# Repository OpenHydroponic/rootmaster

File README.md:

# RootMaster

RootMaster is an open-source hydroponics system designed to help you grow plants efficiently using a soilless solution. This project aims to provide an affordable and customizable solution for home gardeners and small-scale farmers.

## Features

- Automated nutrient delivery system
- pH and EC monitoring
- Temperature and humidity control
- Remote monitoring and control via a web interface
- Modular design for easy expansion

## Documentation

https://openhydroponics.com/hw/rootmaster

## License

This project is licensed under the CERN Open Hardware License. See the [LICENSE](LICENSE) file for details.

## Contact

For questions or support, please open an issue on the [GitLab repository](https://gitlab.com/openhydroponics/hw/rootmaster/-/issues).

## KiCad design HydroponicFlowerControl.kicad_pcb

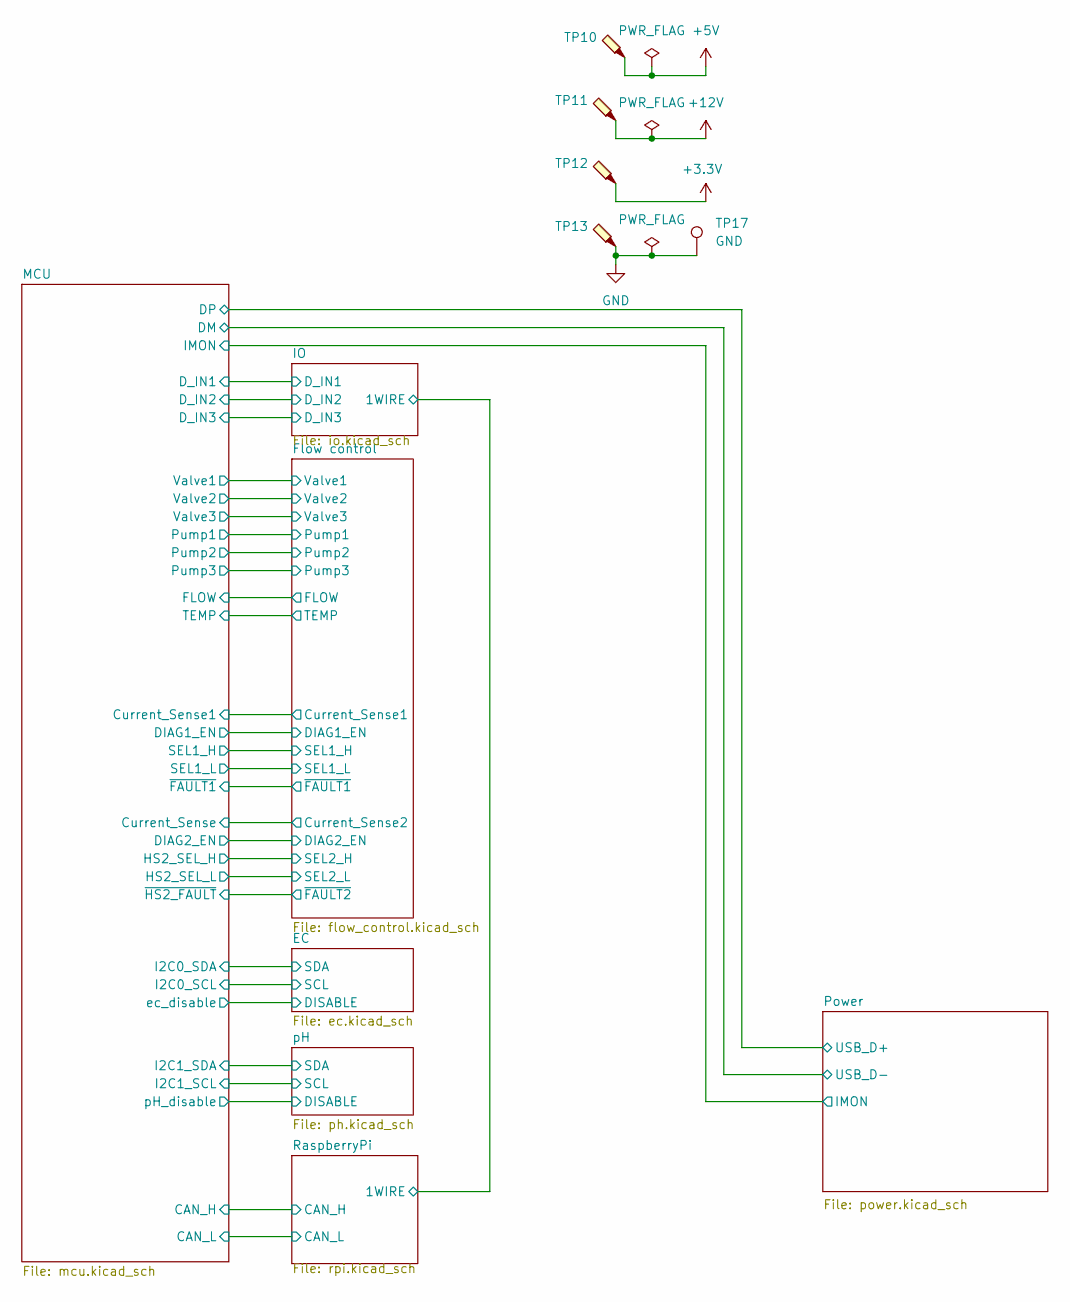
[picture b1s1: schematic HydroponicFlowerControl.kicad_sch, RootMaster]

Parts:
TP10: 5V; TestPoint_Pad_D1.0mm
TP11: 12V; TestPoint_Pad_D1.0mm
TP12: 3.3V; TestPoint_Pad_D1.0mm
TP13: GND; TestPoint_Loop_D1.80mm_Drill1.0mm_Beaded; LCSC C5199801
TP17: GND; TestPoint_Pad_D1.5mm

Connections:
+3.3V: TP12.1 (1_1); also elsewhere on the board
+5V: TP10.1 (1_1); also elsewhere on the board
+12V: TP11.1 (1_1); also elsewhere on the board
GND: TP13.1 (1_1), TP17.1 (1_1); also elsewhere on the board

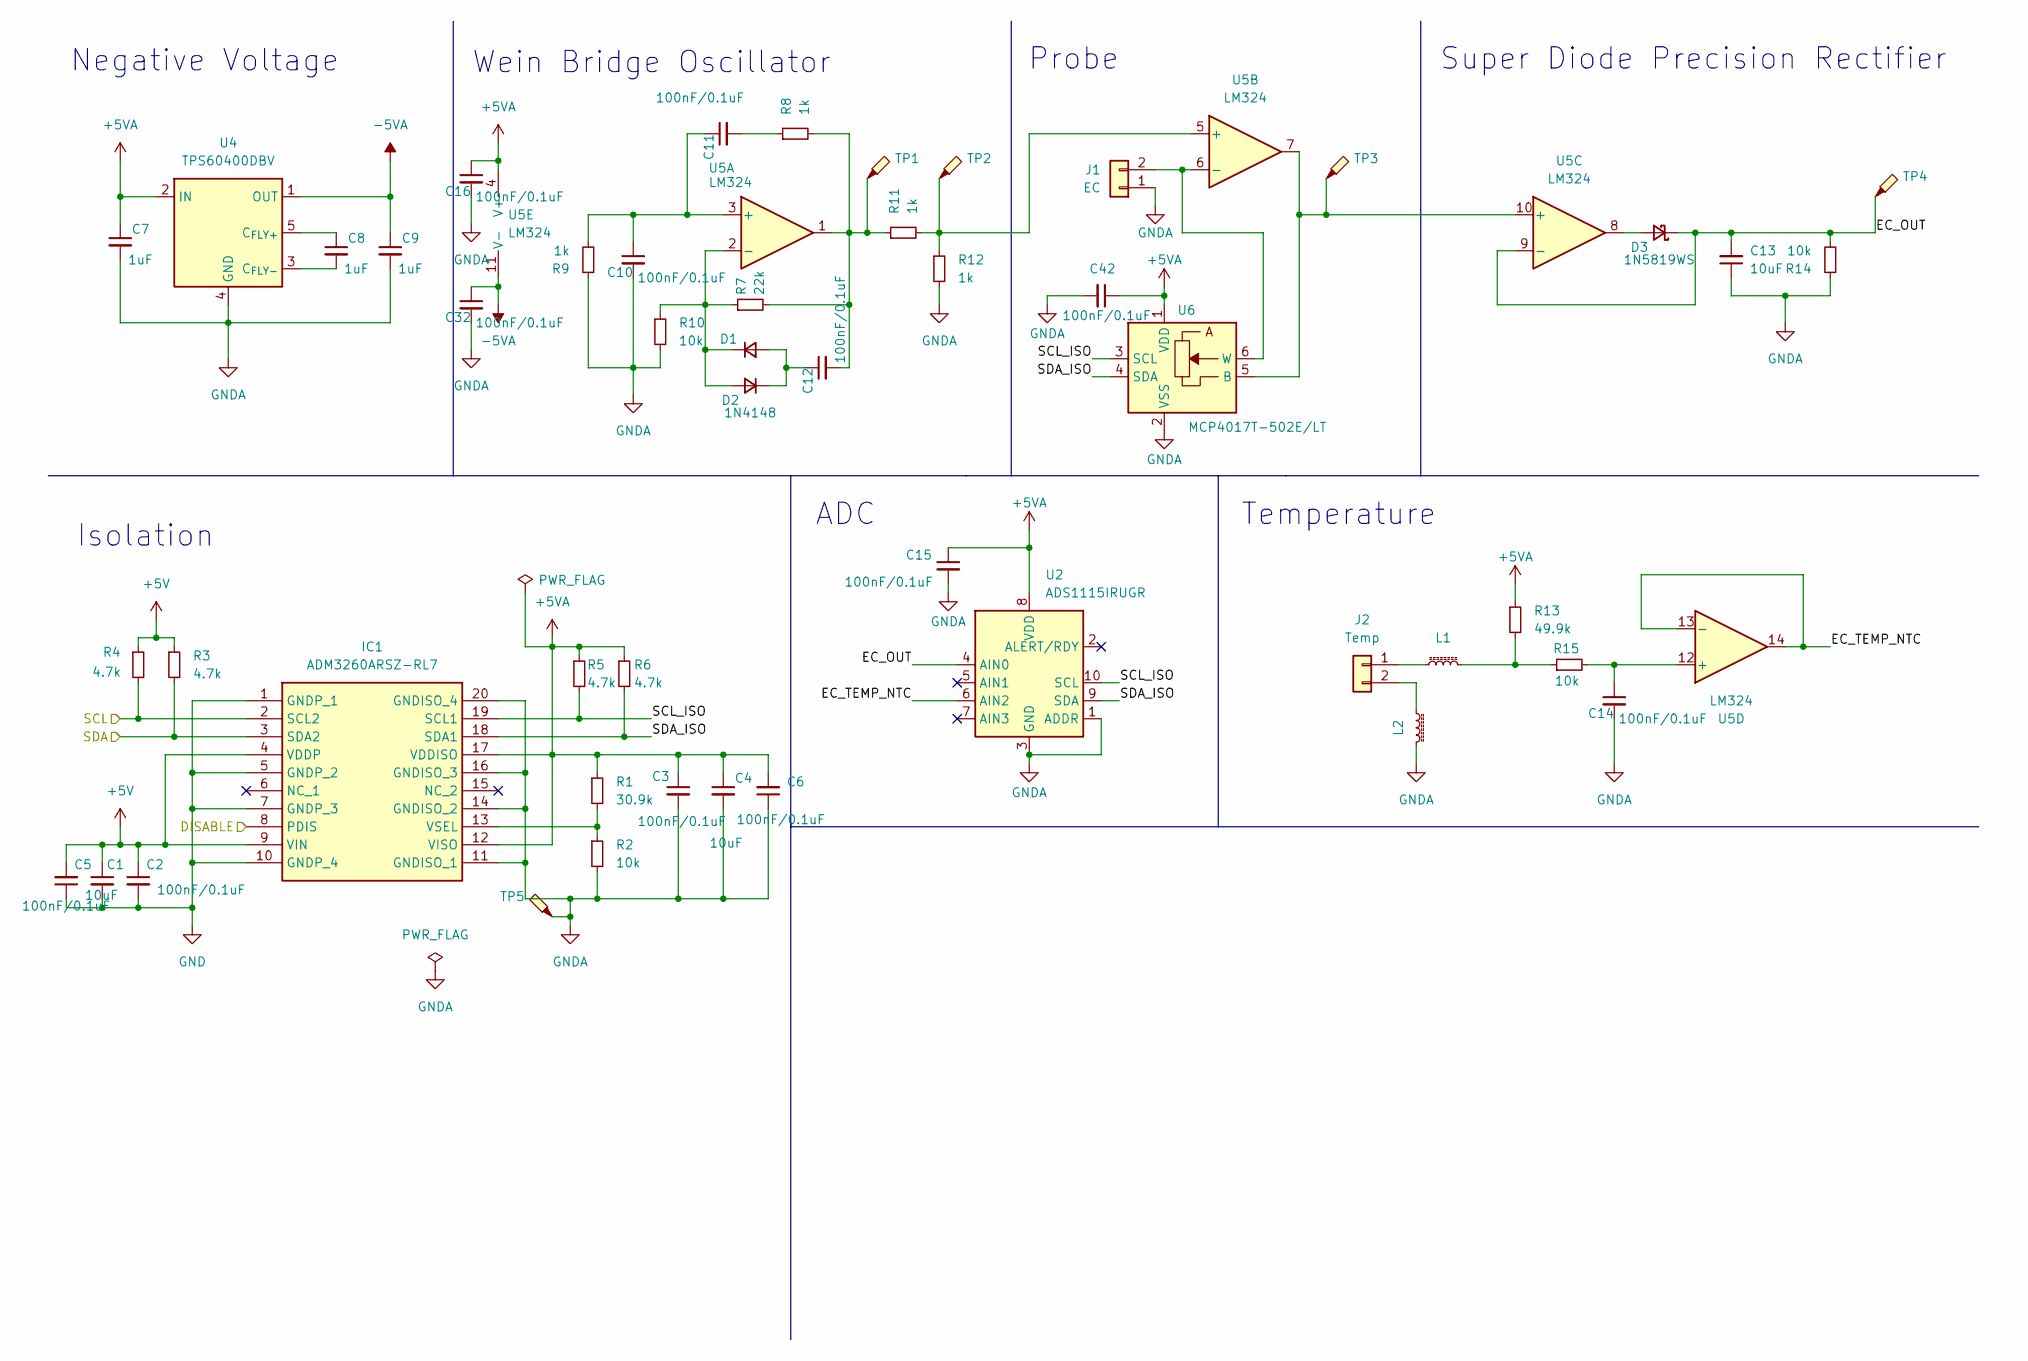
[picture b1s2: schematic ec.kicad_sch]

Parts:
C1, C4: 10uF; C_0603_1608Metric; LCSC C19702
C2, C3, C5, C6, C10, C11, C12, C14, C16, C32, C42: 100nF/0.1uF; C_0603_1608Metric; LCSC C14663
C7, C8, C9: 1uF; C_0603_1608Metric; LCSC C15849
C13: 10uF; C_0805_2012Metric; LCSC C15850
C15: 100nF/0.1uF; C_0402_1005Metric; LCSC C1525
D1, D2: 1N4148; D_SOD-323; LCSC C2128
D3: 1N5819WS; D_SOD-323; LCSC C191023
IC1: ADM3260ARSZ-RL7; SOP65P780X200-20N; Mouser Part Number 584-ADM3260ARSZ-RL7
J1, J2: S2B-XH-A(LF)(SN); JST_XH_S2B-XH-A_1x02_P2.50mm_Horizontal; LCSC C157931
L1, L2: L_Ferrite_Small; L_0603_1608Metric; LCSC C1002
R1: 30.9k; R_0603_1608Metric; LCSC C2930090
R2, R10, R14, R15: 10k; R_0603_1608Metric; LCSC C25804
R3, R4, R5, R6: 4.7k; R_0603_1608Metric; LCSC C23162
R7: 22k; R_0603_1608Metric; LCSC C31850
R8, R9, R11, R12: 1k; R_0603_1608Metric; LCSC C21190
R13: 49.9k; R_0603_1608Metric; LCSC C23184
TP1, TP2, TP3: TestPoint_Small; TestPoint_Pad_D1.0mm
TP4: EC; TestPoint_Pad_D1.0mm
TP5: GNDA; TestPoint_Loop_D1.80mm_Drill1.0mm_Beaded
U2: ADS1115IRUGR; Texas_UQFN-10_1.5x2mm_P0.5mm; LCSC C2651328
U4: TPS60400DBV; SOT-23-5; LCSC C9839
U5: LM324; SOIC-14_3.9x8.7mm_P1.27mm; LCSC C71035
U6: MCP4017T-502E/LT; SOT-363_SC-70-6; LCSC C511303

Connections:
+5V: C1.1, C2.1, C5.2, IC1.4 (VDDP), IC1.9 (VIN), R3.1, R4.1; also elsewhere on the board
+5VA: C3.1, C4.1, C6.2, C7.1, C15.1, C16.1, C42.1, IC1.12 (VISO), IC1.17 (VDDISO), R1.1, R5.1, R6.1, R13.1, U2.8 (VDD), U4.2 (IN), U5.4 (V+), U6.1 (VDD)
-5VA: C9.1, C32.1, U4.1 (OUT), U5.11 (V-)
/EC/DISABLE: IC1.8 (PDIS); also elsewhere on the board
/EC/EC_OUT: C13.2, D3.1 (K), R14.2, TP4.1 (1_1), U2.4 (AIN0), U5.9 (-)
/EC/EC_TEMP_NTC: U2.6 (AIN2), U5.13 (-), U5.14
/EC/SCL: IC1.2 (SCL2), R4.2; also elsewhere on the board
/EC/SCL_ISO: IC1.19 (SCL1), R5.2, U2.10 (SCL), U6.3 (SCL)
/EC/SDA: IC1.3 (SDA2), R3.2; also elsewhere on the board
/EC/SDA_ISO: IC1.18 (SDA1), R6.2, U2.9 (SDA), U6.4 (SDA)
GND: C1.2, C2.2, C5.1, IC1.1 (GNDP_1), IC1.5 (GNDP_2), IC1.7 (GNDP_3), IC1.10 (GNDP_4); also elsewhere on the board
GNDA: C3.2, C4.2, C6.1, C7.2, C9.2, C10.2, C13.1, C14.2, C15.2, C16.2, C32.2, C42.2, IC1.11 (GNDISO_1), IC1.14 (GNDISO_2), IC1.16 (GNDISO_3), IC1.20 (GNDISO_4), J1.1, L2.2, R2.2, R9.1, R10.2, R12.2, R14.1, TP5.1 (1_1), U2.1 (ADDR), U2.3 (GND), U4.4 (GND), U6.2 (VSS)
unnamed: C11.2, R8.1
unnamed: C12.2, R7.2, R8.2, R11.1, TP1.1 (1_1), U5.1
unnamed: C12.1, D1.2 (A), D2.1 (K)
unnamed: D1.1 (K), D2.2 (A), R7.1, R10.1, U5.2 (-)
unnamed: D3.2 (A), U5.8
unnamed: IC1.13 (VSEL), R1.2, R2.1
unnamed: J1.2, U5.6 (-), U6.6 (W)
unnamed: J2.1, L1.1
unnamed: J2.2, L2.1
unnamed: L1.2, R13.2, R15.1
unnamed: C8.1, U4.5 (C_{FLY+})
unnamed: C8.2, U4.3 (C_{FLY-})
unnamed: C10.1, C11.1, R9.2, U5.3 (+)
unnamed: R11.2, R12.1, TP2.1 (1_1), U5.5 (+)
unnamed: TP3.1 (1_1), U5.7, U5.10 (+), U6.5 (B)
unnamed: C14.1, R15.2, U5.12 (+)

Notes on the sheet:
Super Diode Precision Rectifier
Probe
Negative Voltage
Temperature
Wein Bridge Oscillator
ADC
Isolation

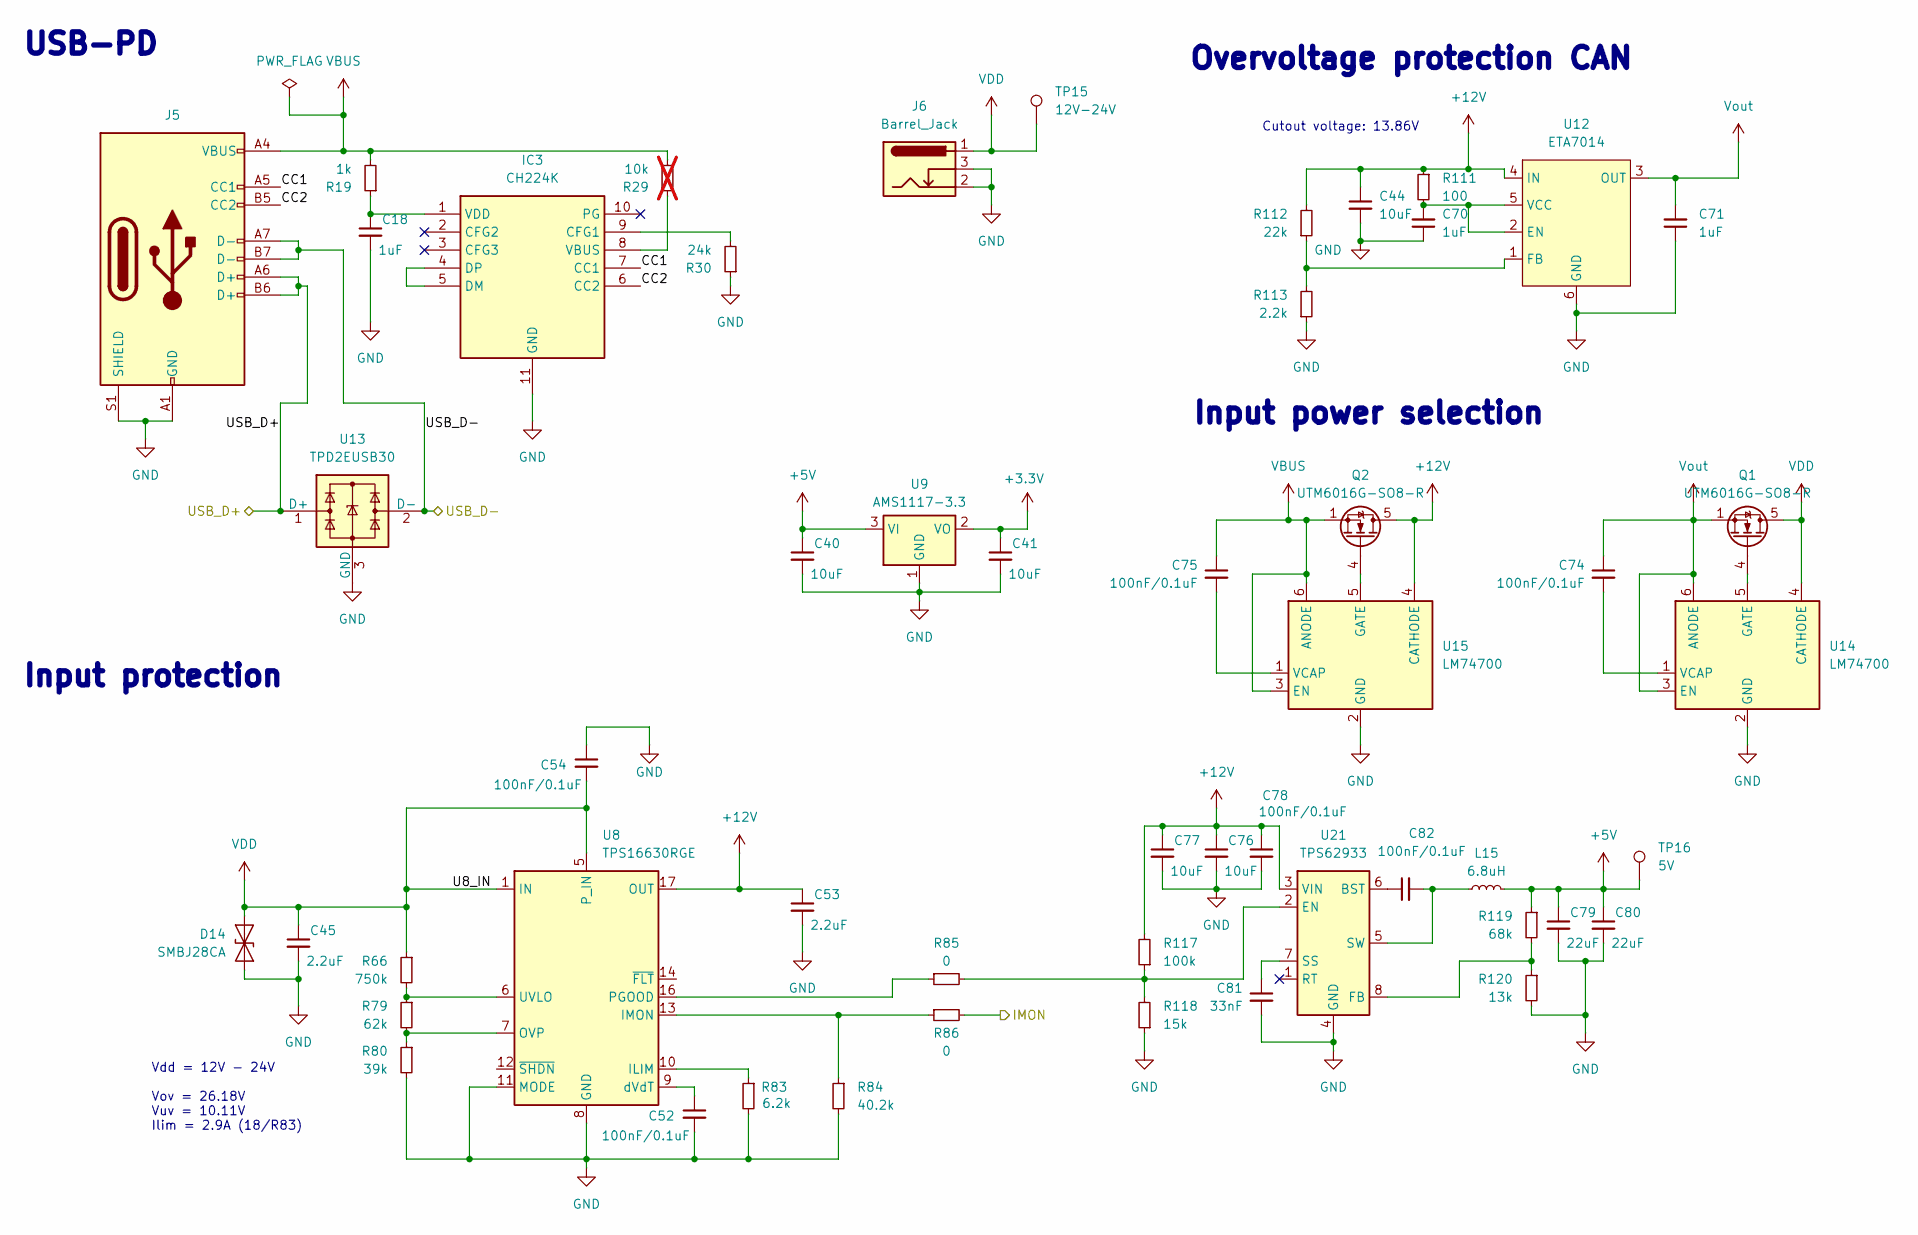
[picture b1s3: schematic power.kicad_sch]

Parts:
C18, C70, C71: 1uF; C_0603_1608Metric; LCSC C15849
C40, C41, C44: 10uF; C_0603_1608Metric; LCSC C19702
C45, C53: 2.2uF; C_1206_3216Metric; LCSC C50254
C52: 100nF/0.1uF; C_0402_1005Metric; LCSC C1525
C54, C78, C82: 100nF/0.1uF; C_0402_1005Metric; LCSC C307331
C74, C75: 100nF/0.1uF; C_0603_1608Metric; LCSC C14663
C76, C77: 10uF; C_1206_3216Metric; LCSC C13585
C79, C80: 22uF; C_1206_3216Metric; LCSC C12891
C81: 33nF; C_0603_1608Metric; LCSC C21117
D14: SMBJ28CA; D_SMB; LCSC C19077583
IC3: CH224K; SOP100P600X180-11N; Manufacturer_Part_Number CH224K; LCSC C970725
J5: USB_C_Receptacle_USB2.0; USB_C_Receptacle_HRO_TYPE-C-31-M-12; LCSC C165948
J6: Barrel_Jack; BarrelJack_XKB_DC_005_5A_2.5_SMT_Horizontal; LCSC C319133
L15: 6.8uH; L_Sunlord_SWPA5040S; LCSC C36411
Q1, Q2: UTM6016G-SO8-R; SOIC-8_3.9x4.9mm_P1.27mm; LCSC C84901
R19: 1k; R_0603_1608Metric; LCSC C21190
R29: 10k; R_0603_1608Metric; LCSC C25804; not fitted
R30: 24k; R_0603_1608Metric; LCSC C23352
R66: 750k; R_0603_1608Metric; LCSC C23240
R79: 62k; R_0603_1608Metric; LCSC C23221
R80: 39k; R_0402_1005Metric; LCSC C25783
R83: 6.2k; R_0603_1608Metric; LCSC C4260
R84: 40.2k; R_0603_1608Metric; LCSC C12447
R85, R86: 0; R_0402_1005Metric; LCSC C17168
R111: 100; R_0402_1005Metric; LCSC C25076
R112: 22k; R_0402_1005Metric; LCSC C25768
R113: 2.2k; R_0402_1005Metric; LCSC C25879
R117: 100k; R_0603_1608Metric; LCSC C25803
R118: 15k; R_0603_1608Metric; LCSC C22809
R119: 68k; R_0603_1608Metric; LCSC C23231
R120: 13k; R_0603_1608Metric; LCSC C22797
TP15: 12V-24V; TestPoint_Pad_D1.5mm
TP16: 5V; TestPoint_Pad_D1.5mm
U8: TPS16630RGE; Texas_RGE0024H_VQFN-24-1EP_4x4mm_P0.5mm_EP2.7x2.7mm_Thermal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; LCSC C1850279
U9: AMS1117-3.3; SOT-223-3_TabPin2; LCSC C6186
U12: ETA7014; SOT-23-6; LCSC C7465500
U13: TPD2EUSB30; SOT-723; LCSC C2844720
U14, U15: LM74700; SOT-23-6; LCSC C2941042
U21: TPS62933; SOT-583-8; LCSC C3200405

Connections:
+3.3V: C41.1, U9.2 (VO); also elsewhere on the board
+5V: C40.1, C79.1, C80.1, L15.2, R119.1, TP16.1 (1_1), U9.3 (VI); also elsewhere on the board
+12V: C44.1, C53.1, C76.1, C77.1, C78.1, Q2.5 (D), Q2.6 (D), Q2.7 (D), Q2.8 (D), R111.1, R112.2, R117.2, U8.17 (OUT), U8.18 (OUT), U12.4 (IN), U15.4 (CATHODE), U21.3 (VIN); also elsewhere on the board
/MCU/IMON: R86.2; also elsewhere on the board
/Power/CC1: IC3.7 (CC1), J5.A5 (CC1)
/Power/CC2: IC3.6 (CC2), J5.B5 (CC2)
/Power/USB_D+: J5.A6 (D+), J5.B6 (D+), U13.1 (D+); also elsewhere on the board
/Power/USB_D-: J5.A7 (D-), J5.B7 (D-), U13.2 (D-); also elsewhere on the board
GND: C18.2, C40.2, C41.2, C44.2, C45.2, C52.2, C53.2, C54.1, C70.1, C71.1, C76.2, C77.2, C78.2, C79.2, C80.2, C81.2, D14.2 (A2), IC3.11 (GND), J5.A1 (GND), J5.A12 (GND), J5.B1 (GND), J5.B12 (GND), J5.S1 (SHIELD), J6.2, J6.3, R30.1, R80.2, R83.2, R84.2, R113.1, R118.1, R120.2, U8.8 (GND), U8.11 (MODE), U8.25 (GND), U9.1 (GND), U12.6 (GND), U13.3 (GND), U14.2 (GND), U15.2 (GND), U21.4 (GND); also elsewhere on the board
unnamed: IC3.9 (CFG1), R30.2
unnamed: IC3.4 (DP), IC3.5 (DM)
unnamed: IC3.8 (VBUS), R29.1
unnamed: C18.1, IC3.1 (VDD), R19.1
unnamed: Q1.4 (G), U14.5 (GATE)
unnamed: Q2.4 (G), U15.5 (GATE)
unnamed: R83.1, U8.10 (ILIM)
unnamed: R84.1, R86.1, U8.13 (IMON)
unnamed: R79.2, R80.1, U8.7 (OVP)
unnamed: R85.1, U8.16 (PGOOD)
unnamed: R66.2, R79.1, U8.6 (UVLO)
unnamed: C52.1, U8.9 (dVdT)
unnamed: C70.2, R111.2, U12.2 (EN), U12.5 (VCC)
unnamed: R112.1, R113.2, U12.1 (FB)
unnamed: C74.2, U14.1 (VCAP)
unnamed: C75.2, U15.1 (VCAP)
unnamed: C82.1, U21.6 (BST)
unnamed: R85.2, R117.1, R118.2, U21.2 (EN)
unnamed: R119.2, R120.1, U21.8 (FB)
unnamed: C81.1, U21.7 (SS)
unnamed: C82.2, L15.1, U21.5 (SW)
VBUS: C75.1, J5.A4 (VBUS), J5.A9 (VBUS), J5.B4 (VBUS), J5.B9 (VBUS), Q2.1 (S), Q2.2 (S), Q2.3 (S), R19.2, R29.2, U15.3 (EN), U15.6 (ANODE)
VDD: C45.1, C54.2, D14.1 (A1), J6.1, Q1.5 (D), Q1.6 (D), Q1.7 (D), Q1.8 (D), R66.1, TP15.1 (1_1), U8.1 (IN), U8.2 (IN), U8.5 (P_IN), U14.4 (CATHODE)
Vout: C71.2, C74.1, Q1.1 (S), Q1.2 (S), Q1.3 (S), U12.3 (OUT), U14.3 (EN), U14.6 (ANODE); also elsewhere on the board

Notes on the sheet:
Overvoltage protection CAN
USB-PD
Input protection
Input power selection
Vdd = 12V - 24V Vov = 26.18V Vuv = 10.11V Ilim = 2.9A (18/R83)
Cutout voltage: 13.86V

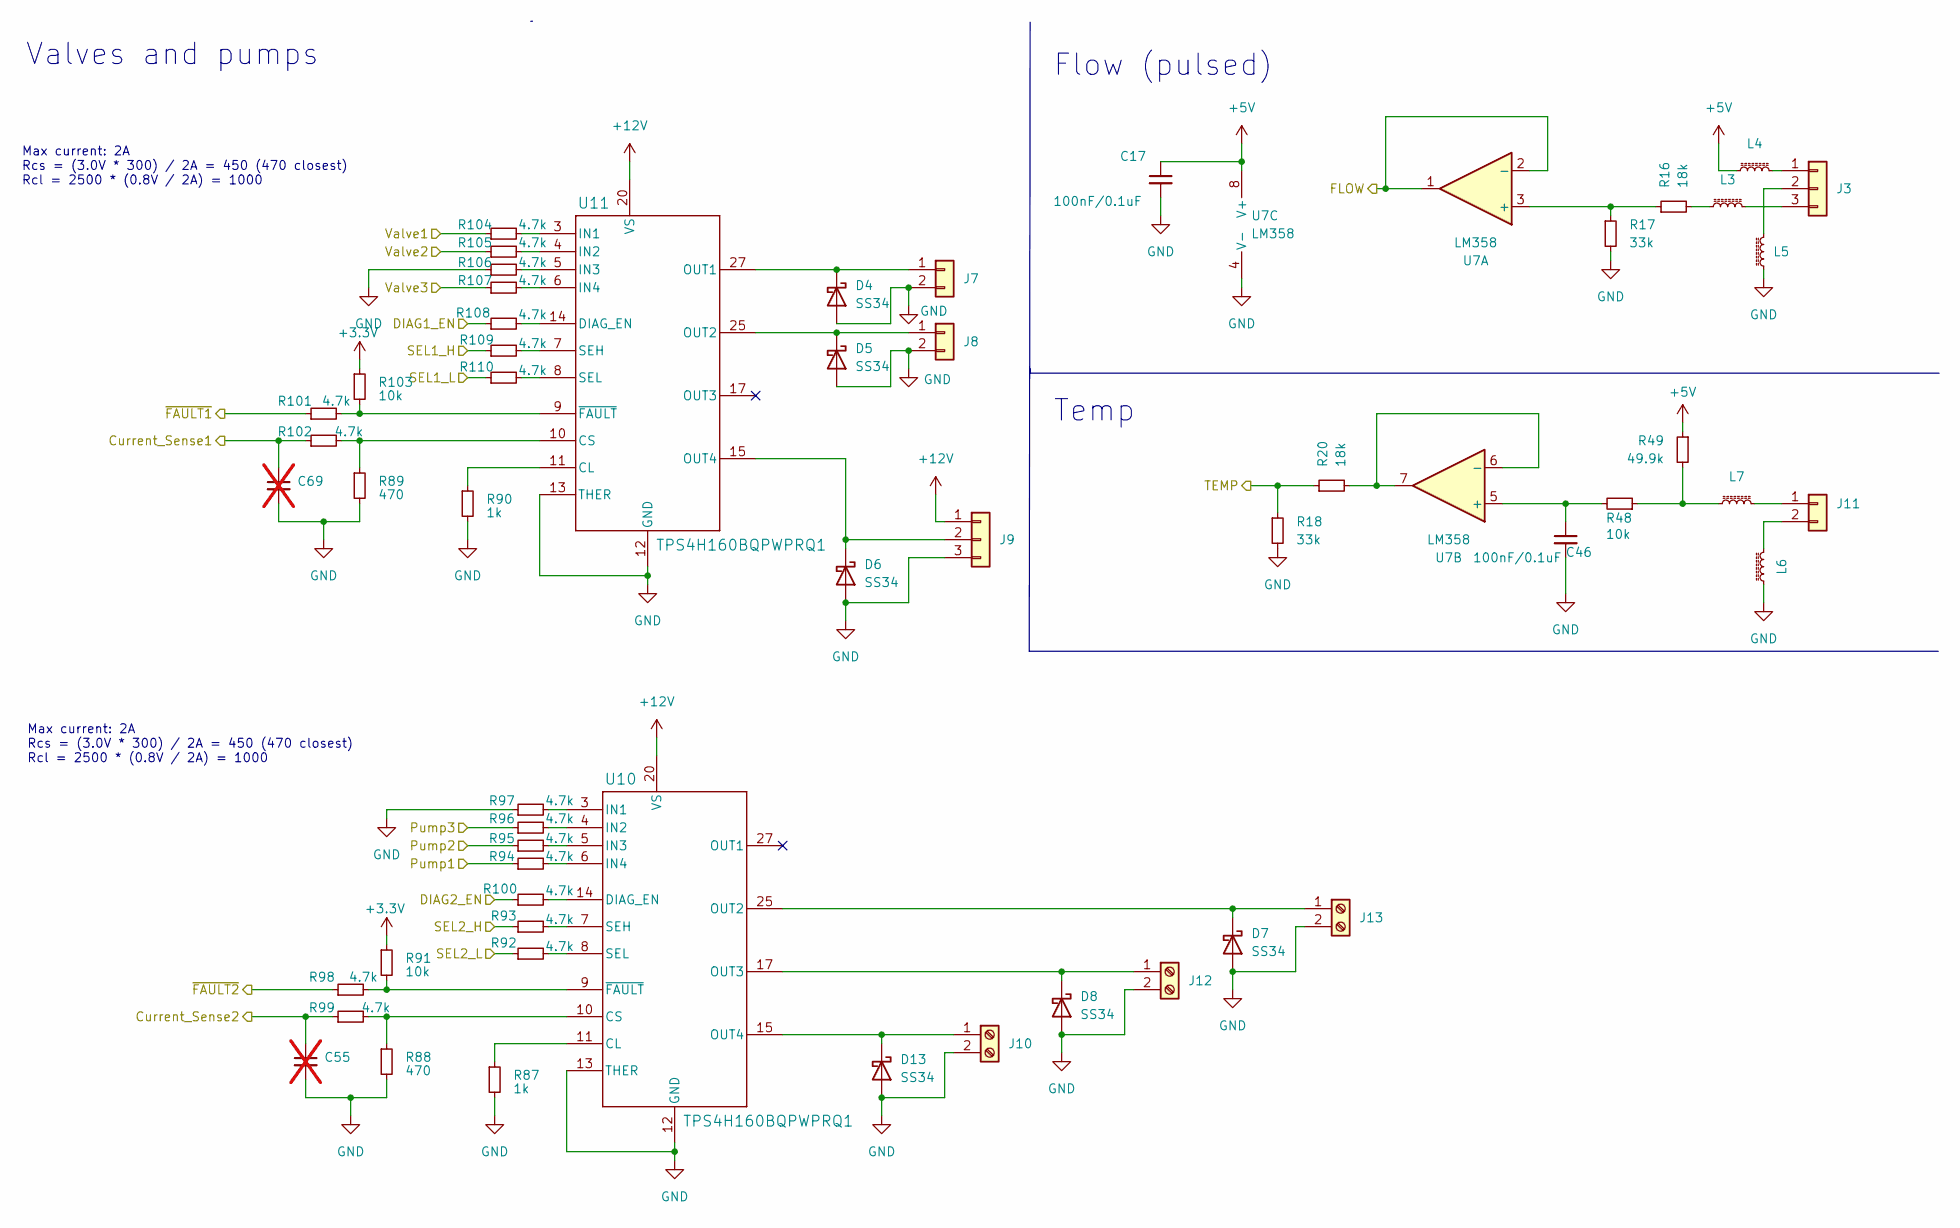
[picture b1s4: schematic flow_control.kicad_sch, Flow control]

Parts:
C17, C46: 100nF/0.1uF; C_0603_1608Metric; LCSC C14663
C55, C69: C_0402_1005Metric; not fitted
D4, D5, D6, D7, D8, D13: SS34; D_SMA; LCSC C8678
J3, J9: S3B-XH-A(LF)(SN); JST_XH_S3B-XH-A_1x03_P2.50mm_Horizontal; LCSC C157928
J7, J8, J11: S2B-XH-A(LF)(SN); JST_XH_S2B-XH-A_1x02_P2.50mm_Horizontal; LCSC C157931
J10, J12, J13: PhoenixContact_MC_1,5_2-G-3.81; PhoenixContact_MC_1,5_2-G-3.81_1x02_P3.81mm_Horizontal; LCSC C5188157
L3, L4, L5, L6, L7: L_Ferrite_Small; L_0603_1608Metric; LCSC C1002
R16, R20: 18k; R_0603_1608Metric; LCSC C25810
R17, R18: 33k; R_0603_1608Metric; LCSC C4216
R48: 10k; R_0603_1608Metric; LCSC C25804
R49: 49.9k; R_0603_1608Metric; LCSC C23184
R87, R90: 1k; R_0402_1005Metric; LCSC C11702
R88, R89: 470; R_0402_1005Metric; LCSC C25117
R91, R103: 10k; R_0402_1005Metric; LCSC C25744
R92, R93, R94, R95, R96, R97, R98, R99, R100, R101, R102, R104, R105, R106, R107, R108, R109, R110: 4.7k; R_0402_1005Metric; LCSC C25900
U7: LM358; SOIC-8_3.9x4.9mm_P1.27mm; LCSC C7950
U10, U11: TPS4H160BQPWPRQ1; HTSSOP-28-1EP_4.4x9.7mm_P0.65mm_EP2.85x5.4mm_ThermalVias; LCSC C471053

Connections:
+3.3V: R91.1, R103.1; also elsewhere on the board
+5V: C17.1, L4.1, R49.1, U7.8 (V+); also elsewhere on the board
+12V: J9.1, U10.20 (VS), U10.21 (VS), U10.22 (VS), U10.23 (VS), U11.20 (VS), U11.21 (VS), U11.22 (VS), U11.23 (VS); also elsewhere on the board
/Flow control/Current_Sense1: C69.1, R102.1; also elsewhere on the board
/Flow control/Current_Sense2: C55.1, R99.1; also elsewhere on the board
/Flow control/DIAG1_EN: R108.1; also elsewhere on the board
/Flow control/DIAG2_EN: R100.1; also elsewhere on the board
/Flow control/FLOW: U7.1, U7.2 (-); also elsewhere on the board
/Flow control/Pump1: R94.1; also elsewhere on the board
/Flow control/Pump2: R95.1; also elsewhere on the board
/Flow control/Pump3: R96.1; also elsewhere on the board
/Flow control/SEL1_H: R109.1; also elsewhere on the board
/Flow control/SEL1_L: R110.1; also elsewhere on the board
/Flow control/SEL2_H: R93.1; also elsewhere on the board
/Flow control/SEL2_L: R92.1; also elsewhere on the board
/Flow control/TEMP: R18.1, R20.1; also elsewhere on the board
/Flow control/Valve1: R104.1; also elsewhere on the board
/Flow control/Valve2: R105.1; also elsewhere on the board
/Flow control/Valve3: R107.1; also elsewhere on the board
/Flow control/~FAULT1: R101.1; also elsewhere on the board
/Flow control/~FAULT2: R98.1; also elsewhere on the board
GND: C17.2, C46.2, C55.2, C69.2, D4.2 (A), D5.2 (A), D6.2 (A), D7.2 (A), D8.2 (A), D13.2 (A), J7.2, J8.2, J9.3, J10.2, J12.2, J13.2, L5.1, L6.2, R17.2, R18.2, R87.2, R88.2, R89.2, R90.2, R97.1, R106.1, U7.4 (V-), U10.1 (GND), U10.12 (GND), U10.13 (THER), U10.29 (PAD), U11.1 (GND), U11.12 (GND), U11.13 (THER), U11.29 (PAD); also elsewhere on the board
unnamed: D4.1 (K), J7.1, U11.27 (OUT1), U11.28 (OUT1)
unnamed: D5.1 (K), J8.1, U11.25 (OUT2), U11.26 (OUT2)
unnamed: D6.1 (K), J9.2, U11.15 (OUT4), U11.16 (OUT4)
unnamed: D7.1 (K), J13.1, U10.25 (OUT2), U10.26 (OUT2)
unnamed: D8.1 (K), J12.1, U10.17 (OUT3), U10.18 (OUT3)
unnamed: D13.1 (K), J10.1, U10.15 (OUT4), U10.16 (OUT4)
unnamed: J3.1, L4.2
unnamed: J3.2, L5.2
unnamed: J3.3, L3.2
unnamed: J11.1, L7.1
unnamed: J11.2, L6.1
unnamed: L3.1, R16.2
unnamed: L7.2, R48.1, R49.2
unnamed: R16.1, R17.1, U7.3 (+)
unnamed: C46.1, R48.2, U7.5 (+)
unnamed: R20.2, U7.6 (-), U7.7
unnamed: R87.1, U10.11 (CL)
unnamed: R88.1, R99.2, U10.10 (CS)
unnamed: R100.2, U10.14 (DIAG_EN)
unnamed: R97.2, U10.3 (IN1)
unnamed: R96.2, U10.4 (IN2)
unnamed: R95.2, U10.5 (IN3)
unnamed: R94.2, U10.6 (IN4)
unnamed: R93.2, U10.7 (SEH)
unnamed: R92.2, U10.8 (SEL)
unnamed: R91.2, R98.2, U10.9 (~FAULT)
unnamed: R90.1, U11.11 (CL)
unnamed: R89.1, R102.2, U11.10 (CS)
unnamed: R108.2, U11.14 (DIAG_EN)
unnamed: R104.2, U11.3 (IN1)
unnamed: R105.2, U11.4 (IN2)
unnamed: R106.2, U11.5 (IN3)
unnamed: R107.2, U11.6 (IN4)
unnamed: R109.2, U11.7 (SEH)
unnamed: R110.2, U11.8 (SEL)
unnamed: R101.2, R103.2, U11.9 (~FAULT)

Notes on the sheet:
Max current: 2A Rcs = (3.0V * 300) / 2A = 450 (470 closest) Rcl = 2500 * (0.8V / 2A) = 1000
Valves and pumps
Temp
Flow (pulsed)

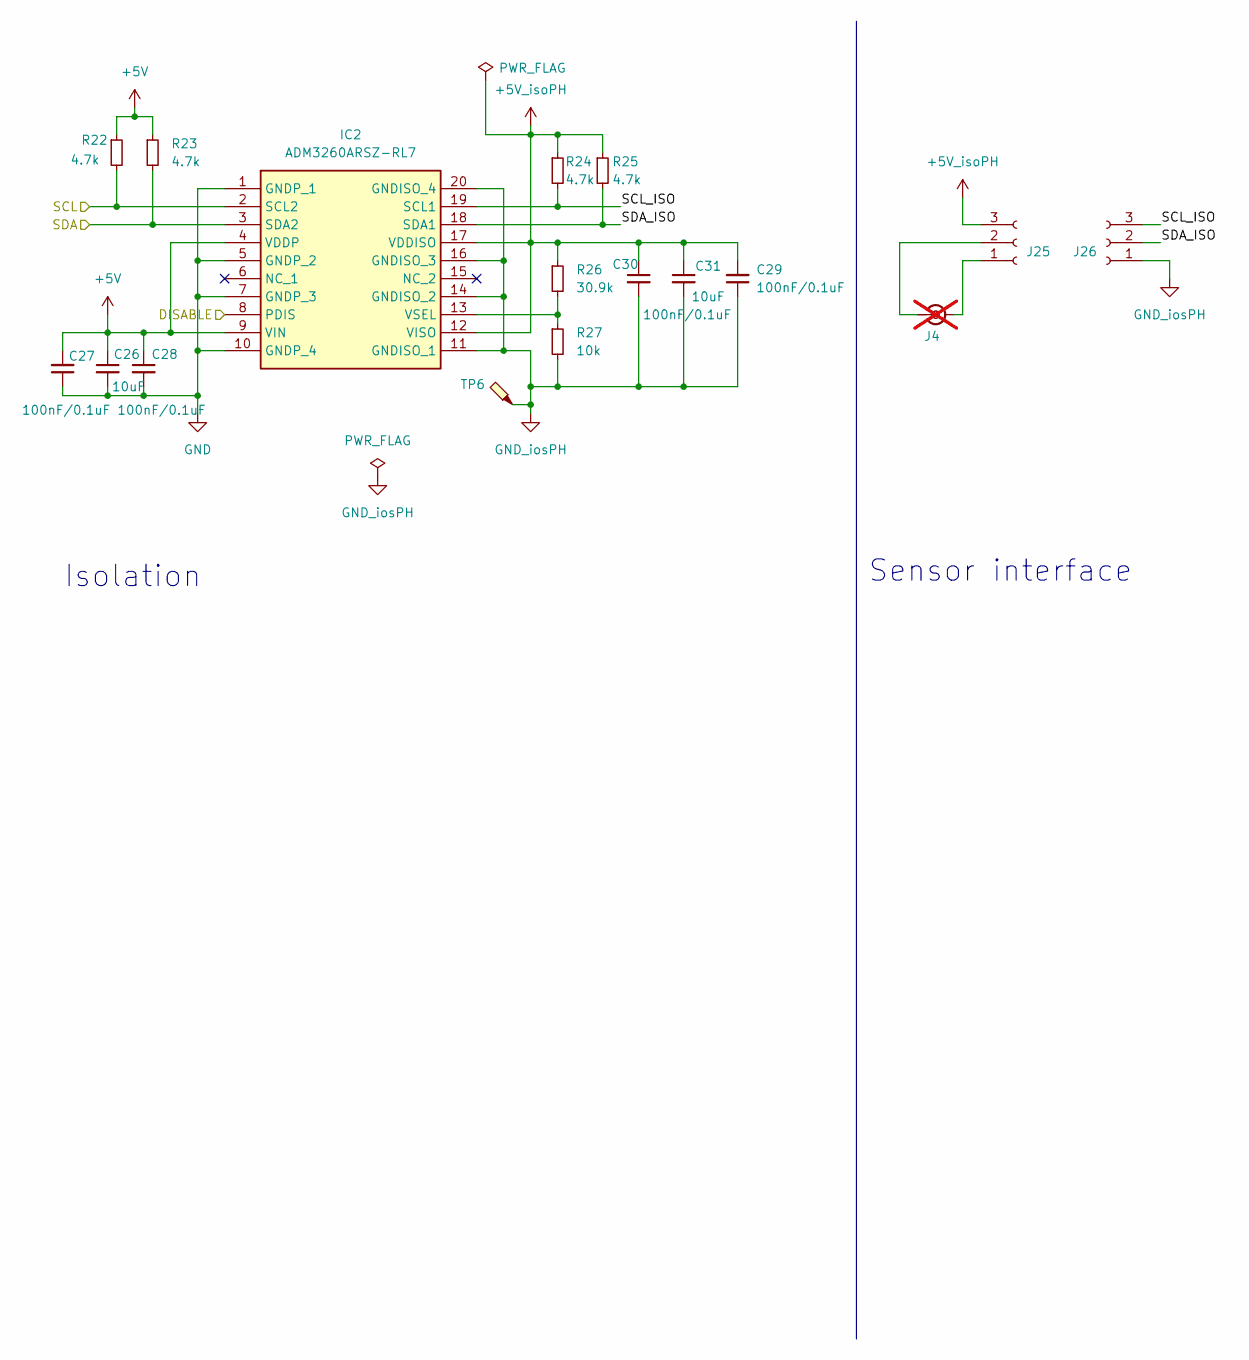
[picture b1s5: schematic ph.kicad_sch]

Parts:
C26, C31: 10uF; C_0603_1608Metric; LCSC C19702
C27, C28, C29, C30: 100nF/0.1uF; C_0603_1608Metric; LCSC C14663
IC2: ADM3260ARSZ-RL7; SOP65P780X200-20N; Mouser Part Number 584-ADM3260ARSZ-RL7
J4: pH; BNC_SMA; LCSC bnc C2837587; not fitted
J25, J26: Conn_01x03_Socket; PinSocket_1x03_P2.54mm_Vertical_SMD_Pin1Left; LCSC C42379196
R22, R23, R24, R25: 4.7k; R_0603_1608Metric; LCSC C23162
R26: 30.9k; R_0603_1608Metric; LCSC C2930090
R27: 10k; R_0603_1608Metric; LCSC C25804
TP6: GND_ISO; TestPoint_Loop_D1.80mm_Drill1.0mm_Beaded; LCSC C5199801

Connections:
+5V: C26.1, C27.2, C28.1, IC2.4 (VDDP), IC2.9 (VIN), R22.1, R23.1; also elsewhere on the board
+5V_isoPH: C29.2, C30.1, C31.1, IC2.12 (VISO), IC2.17 (VDDISO), J25.3, R24.1, R25.1, R26.1
/MCU/I2C1_SCL: IC2.2 (SCL2), R22.2; also elsewhere on the board
/MCU/I2C1_SDA: IC2.3 (SDA2), R23.2; also elsewhere on the board
/MCU/pH_disable: IC2.8 (PDIS); also elsewhere on the board
/pH/SCL_ISO: IC2.19 (SCL1), J26.3, R24.2
/pH/SDA_ISO: IC2.18 (SDA1), J26.2, R25.2
GND: C26.2, C27.1, C28.2, IC2.1 (GNDP_1), IC2.5 (GNDP_2), IC2.7 (GNDP_3), IC2.10 (GNDP_4); also elsewhere on the board
GND_iosPH: C29.1, C30.2, C31.2, IC2.11 (GNDISO_1), IC2.14 (GNDISO_2), IC2.16 (GNDISO_3), IC2.20 (GNDISO_4), J26.1, R27.2, TP6.1 (1_1)
unnamed: IC2.13 (VSEL), R26.2, R27.1
unnamed: J4.2 (Ext), J25.1
unnamed: J4.1 (In), J25.2

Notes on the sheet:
Isolation
Sensor interface

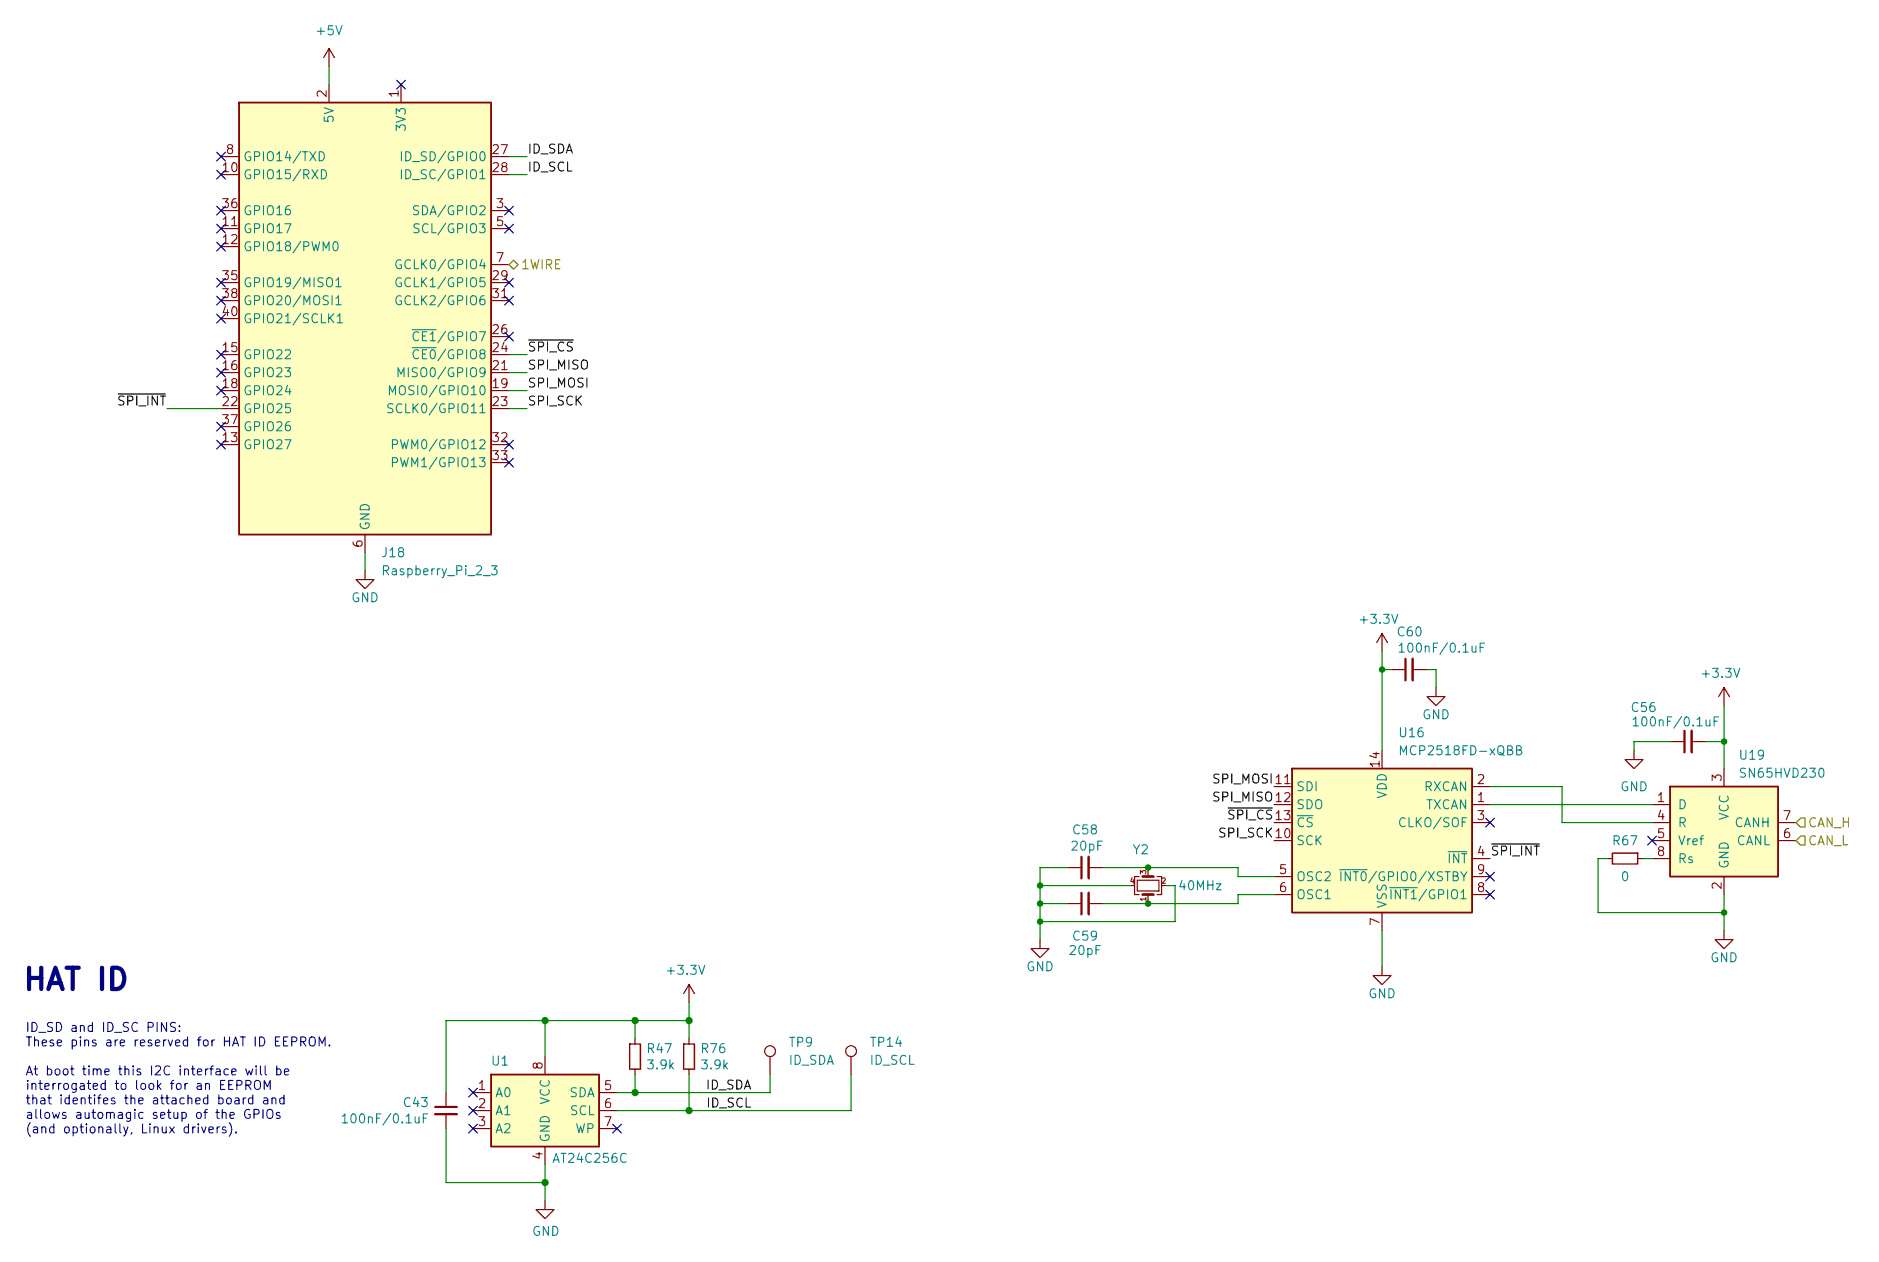
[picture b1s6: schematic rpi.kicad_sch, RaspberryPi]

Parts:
C43, C56, C60: 100nF/0.1uF; C_0603_1608Metric; LCSC C14663
C58, C59: 20pF; C_0603_1608Metric; LCSC C1648
J18: Raspberry_Pi_2_3; HDR-SMD_40P-P2.54-V-F-R2-C20-S7.1-EH; LCSC C2685092
R47, R76: 3.9k; R_0603_1608Metric; LCSC C23018
R67: 0; R_0603_1608Metric; LCSC C21189
TP9: ID_SDA; TestPoint_Pad_D1.5mm
TP14: ID_SCL; TestPoint_Pad_D1.5mm
U1: AT24C256C; SOIC-8_3.9x4.9mm_P1.27mm; LCSC C6482
U16: MCP2518FD-xQBB; SOIC-14_3.9x8.7mm_P1.27mm; LCSC C626758
U19: SN65HVD230; SOIC-8_3.9x4.9mm_P1.27mm; LCSC C12084
Y2: 40MHz; Crystal_SMD_3225-4Pin_3.2x2.5mm; LCSC C9010

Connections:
+3.3V: C43.1, C56.2, C60.1, R47.1, R76.1, U1.8 (VCC), U16.14 (VDD), U19.3 (VCC); also elsewhere on the board
+5V: J18.2 (5V), J18.4 (5V); also elsewhere on the board
/IO/1WIRE: J18.7 (GCLK0/GPIO4); also elsewhere on the board
/MCU/CAN_H: U19.7 (CANH); also elsewhere on the board
/MCU/CAN_L: U19.6 (CANL); also elsewhere on the board
/RaspberryPi/ID_SCL: J18.28 (ID_SC/GPIO1), R76.2, TP14.1 (1_1), U1.6 (SCL)
/RaspberryPi/ID_SDA: J18.27 (ID_SD/GPIO0), R47.2, TP9.1 (1_1), U1.5 (SDA)
/RaspberryPi/SPI_MISO: J18.21 (MISO0/GPIO9), U16.12 (SDO)
/RaspberryPi/SPI_MOSI: J18.19 (MOSI0/GPIO10), U16.11 (SDI)
/RaspberryPi/SPI_SCK: J18.23 (SCLK0/GPIO11), U16.10 (SCK)
/RaspberryPi/~SPI_CS: J18.24 (~CE0/GPIO8), U16.13 (~CS)
/RaspberryPi/~SPI_INT: J18.22 (GPIO25), U16.4 (~INT)
GND: C43.2, C56.1, C58.1, C59.1, C60.2, J18.6 (GND), J18.9 (GND), J18.14 (GND), J18.20 (GND), J18.25 (GND), J18.30 (GND), J18.34 (GND), J18.39 (GND), R67.2, U1.4 (GND), U16.7 (VSS), U16.15 (VSS), U19.2 (GND), Y2.2, Y2.4; also elsewhere on the board
unnamed: C59.2, U16.6 (OSC1), Y2.1
unnamed: C58.2, U16.5 (OSC2), Y2.3
unnamed: U16.2 (RXCAN), U19.4 (R)
unnamed: U16.1 (TXCAN), U19.1 (D)
unnamed: R67.1, U19.8 (Rs)

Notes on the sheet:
ID_SD and ID_SC PINS: These pins are reserved for HAT ID EEPROM. At boot time this I2C interface will be interrogated to look for an EEPROM that identifes the attached board and allows automagic setup of the GPIOs (and optionally, Linux drivers).
HAT ID
